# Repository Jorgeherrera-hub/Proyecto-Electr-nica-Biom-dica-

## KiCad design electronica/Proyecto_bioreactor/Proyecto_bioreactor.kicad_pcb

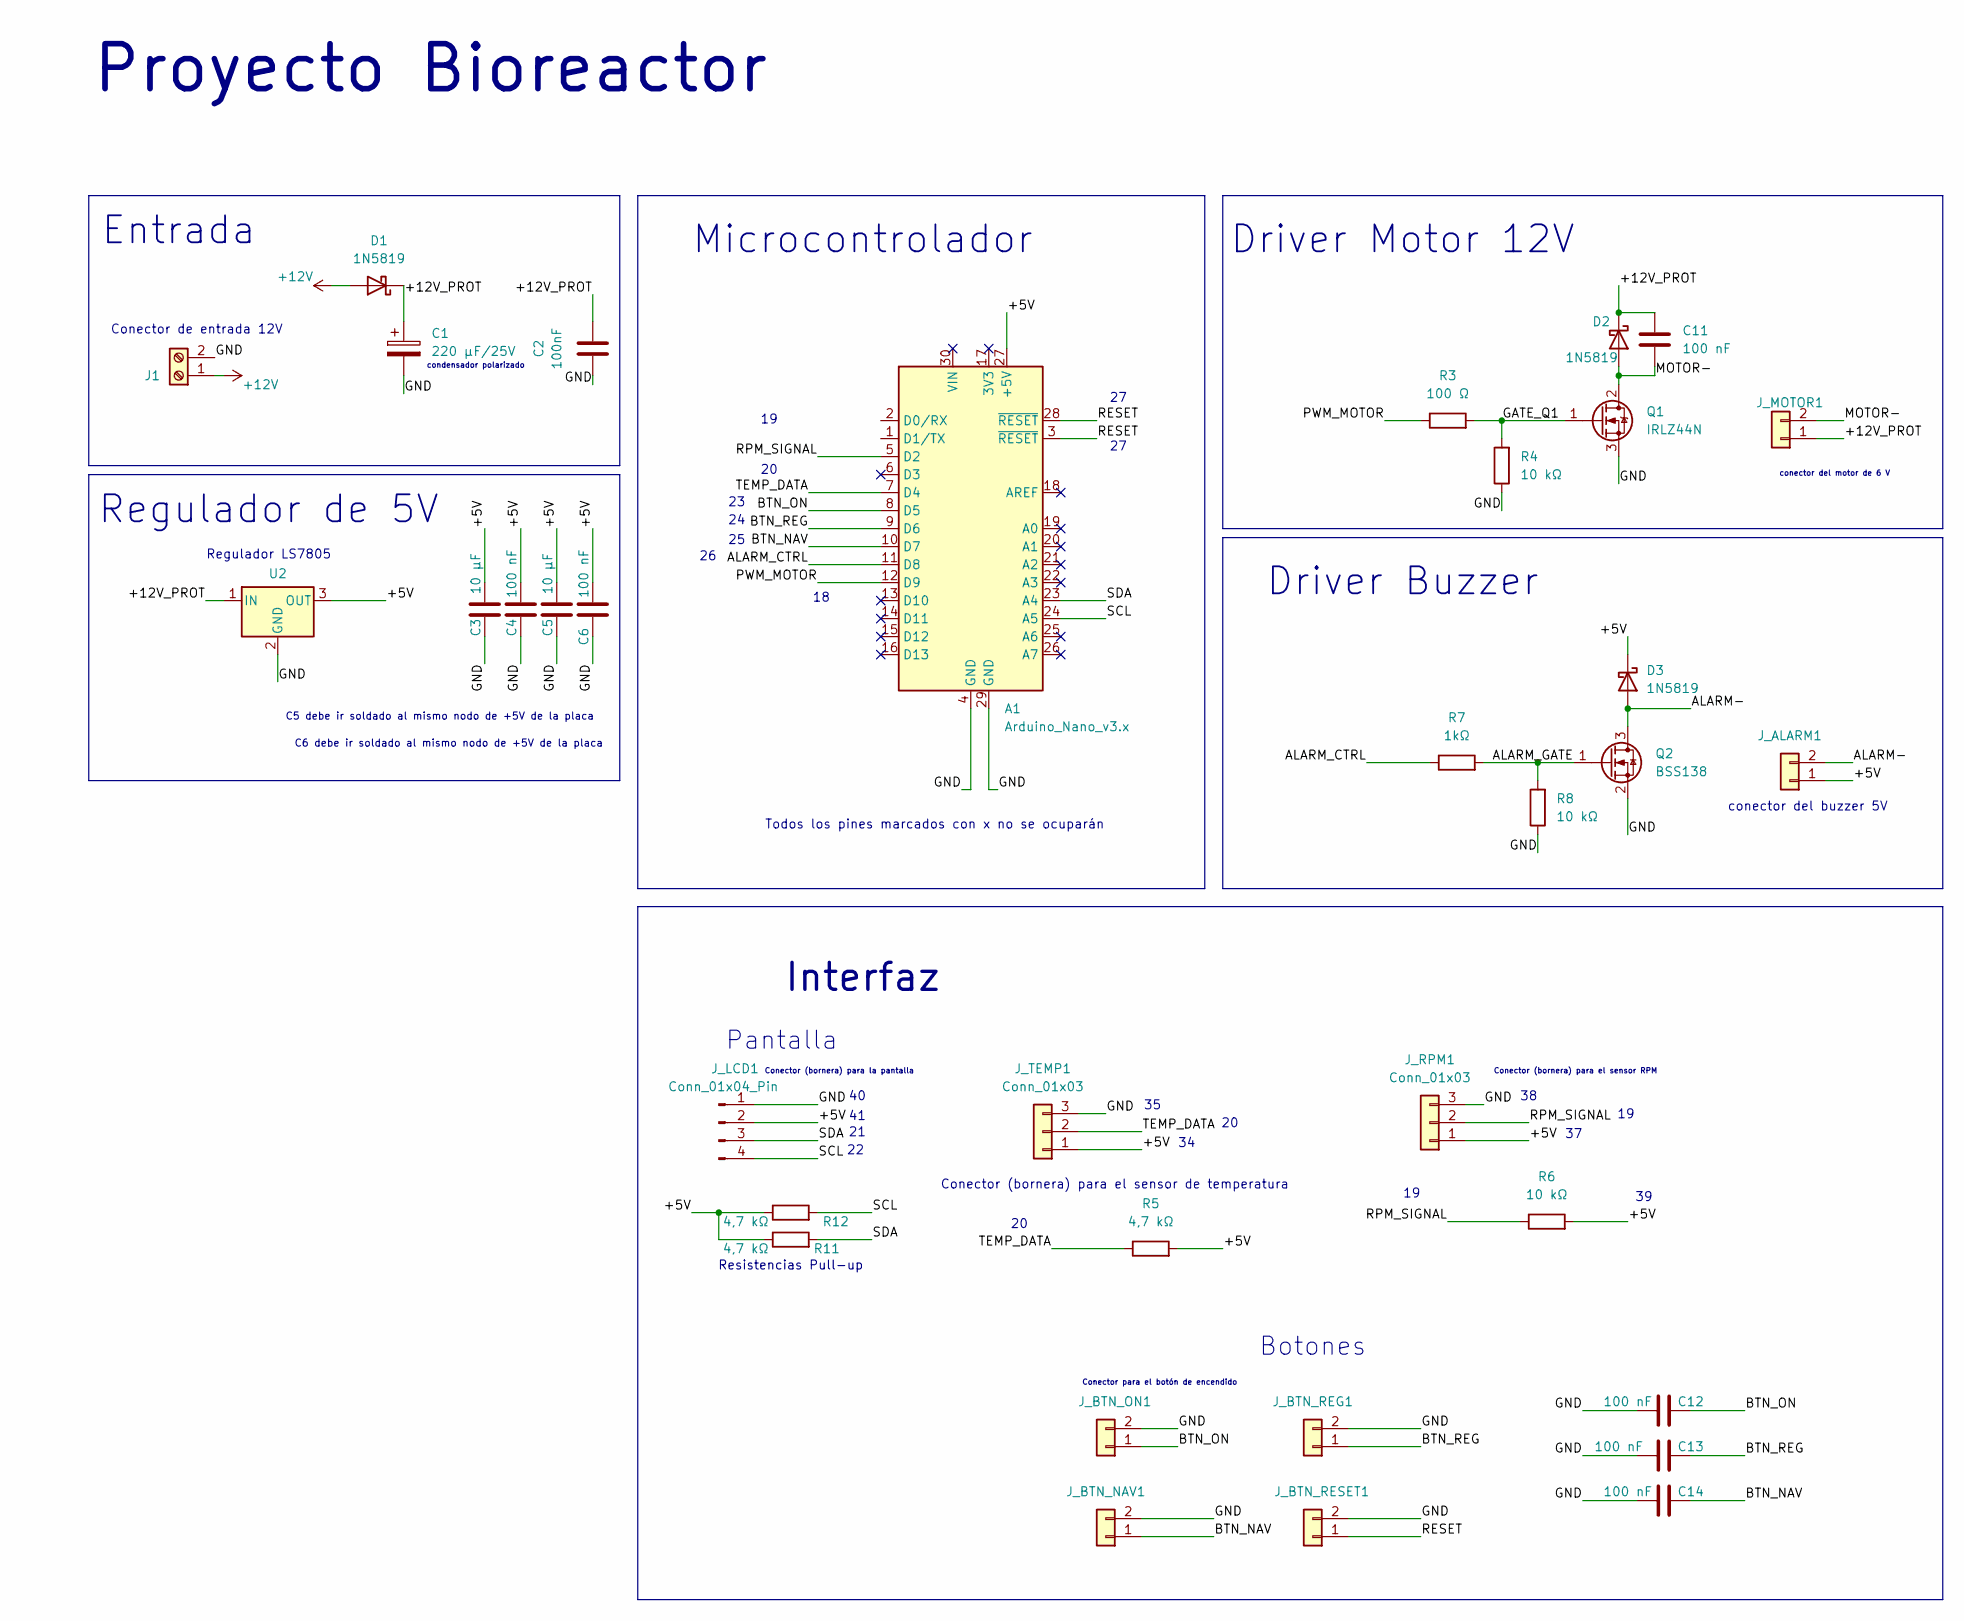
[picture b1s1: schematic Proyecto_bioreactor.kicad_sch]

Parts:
A1: Arduino_Nano_v3.x; Arduino_Nano
C1: 220 µF/25V; CP_Radial_D8.0mm_P3.50mm
C2: 100nF; C_Disc_D5.0mm_W2.5mm_P5.00mm
C3, C5: 10 µF; CP_Radial_D5.0mm_P2.00mm
C4, C6, C11, C12, C13, C14: 100 nF; C_Disc_D5.0mm_W2.5mm_P5.00mm
D1, D2, D3: 1N5819; D_DO-41_SOD81_P10.16mm_Horizontal
J1: Screw_Terminal_01x02; TerminalBlock_Phoenix_MKDS-1,5-2-5.08_1x02_P5.08mm_Horizont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
J_ALARM1: PinHeader_1x02_P2.54mm_Vertical
J_BTN_NAV1: PinHeader_1x02_P2.54mm_Vertical
J_BTN_ON1: PinHeader_1x02_P2.54mm_Vertical
J_BTN_REG1: PinHeader_1x02_P2.54mm_Vertical
J_BTN_RESET1: PinHeader_1x02_P2.54mm_Vertical
J_LCD1: Conn_01x04_Pin; PinHeader_1x04_P2.54mm_Vertical
J_MOTOR1: PinHeader_1x02_P2.54mm_Vertical; TerminalBlock_Phoenix_MKDS-1,5-2-5.08_1x02_P5.08mm_Horizont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
J_RPM1: Conn_01x03; PinHeader_1x03_P2.54mm_Vertical
J_TEMP1: Conn_01x03; PinHeader_1x03_P2.54mm_Vertical
Q1: IRLZ44N; TO-220-3_Vertical
Q2: BSS138; SOT-23
R3: 100 Ω; R_Axial_DIN0204_L3.6mm_D1.6mm_P7.62mm_Horizontal
R4, R6, R8: 10 kΩ; R_Axial_DIN0204_L3.6mm_D1.6mm_P7.62mm_Horizontal
R5, R11, R12: 4,7 kΩ; R_Axial_DIN0204_L3.6mm_D1.6mm_P7.62mm_Horizontal
R7: 1kΩ; R_Axial_DIN0204_L3.6mm_D1.6mm_P7.62mm_Horizontal
U2: OKI-78SR-5/1.5-W36-C (L7805); Converter_DCDC_Murata_OKI-78SR_Vertical

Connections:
+12V: D1.2 (A), J1.1
/+5V: A1.27 (+5V), C3.1, C4.1, C5.1, C6.1, D3.1 (K), J_ALARM1.1, J_LCD1.2, J_RPM1.1, J_TEMP1.1, R5.2, R6.2, R11.1, R12.1, U2.3 (OUT)
/+12V_PROT: C1.1, C2.2, C11.1, D1.1 (K), D2.1 (K), J_MOTOR1.1, U2.1 (IN)
/ALARM-: D3.2 (A), J_ALARM1.2, Q2.3 (D)
/ALARM_CTRL: A1.11 (D8), R7.1
/ALARM_GATE: Q2.1 (G), R7.2, R8.2
/BTN_NAV: A1.10 (D7), J_BTN_NAV1.1
/BTN_NAV: C14.1
/BTN_ON: A1.8 (D5), C12.1, J_BTN_ON1.1
/BTN_REG: A1.9 (D6), J_BTN_REG1.1
/BTN_REG: C13.1
/GATE_Q1: Q1.1 (G), R3.2, R4.2
/GND: A1.4 (GND), A1.29 (GND), C1.2, C2.1, C3.2, C4.2, C5.2, C6.2, C12.2, C13.2, C14.2, J1.2, J_BTN_NAV1.2, J_BTN_ON1.2, J_BTN_REG1.2, J_BTN_RESET1.2, J_LCD1.1, J_RPM1.3, J_TEMP1.3, Q1.3 (S), Q2.2 (S), R4.1, R8.1, U2.2 (GND)
/MOTOR-: C11.2, D2.2 (A), J_MOTOR1.2, Q1.2 (D)
/PWM_MOTOR: A1.12 (D9), R3.1
/RESET: A1.3 (~RESET), A1.28 (~RESET), J_BTN_RESET1.1
/RPM_SIGNAL: A1.5 (D2), J_RPM1.2, R6.1
/SCL: A1.24 (A5), J_LCD1.4, R12.2
/SDA: A1.23 (A4), J_LCD1.3, R11.2
/TEMP_DATA: A1.7 (D4), J_TEMP1.2, R5.1

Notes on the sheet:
Conector (bornera) para el sensor RPM
C6 debe ir soldado al mismo nodo de +5V de la placa
Pantalla
conector del buzzer 5V
Regulador de 5V
Conector de entrada 12V
Todos los pines marcados con x no se ocuparán
Conector para el botón de encendido
condensador polarizado
Driver Buzzer
Conector (bornera) para el sensor de temperatura
conector del motor de 6 V
Regulador LS7805
Botones
Interfaz
Proyecto Bioreactor
Resistencias Pull-up
Microcontrolador
Driver Motor 12V
Entrada
C5 debe ir soldado al mismo nodo de +5V de la placa
Conector (bornera) para la pantalla

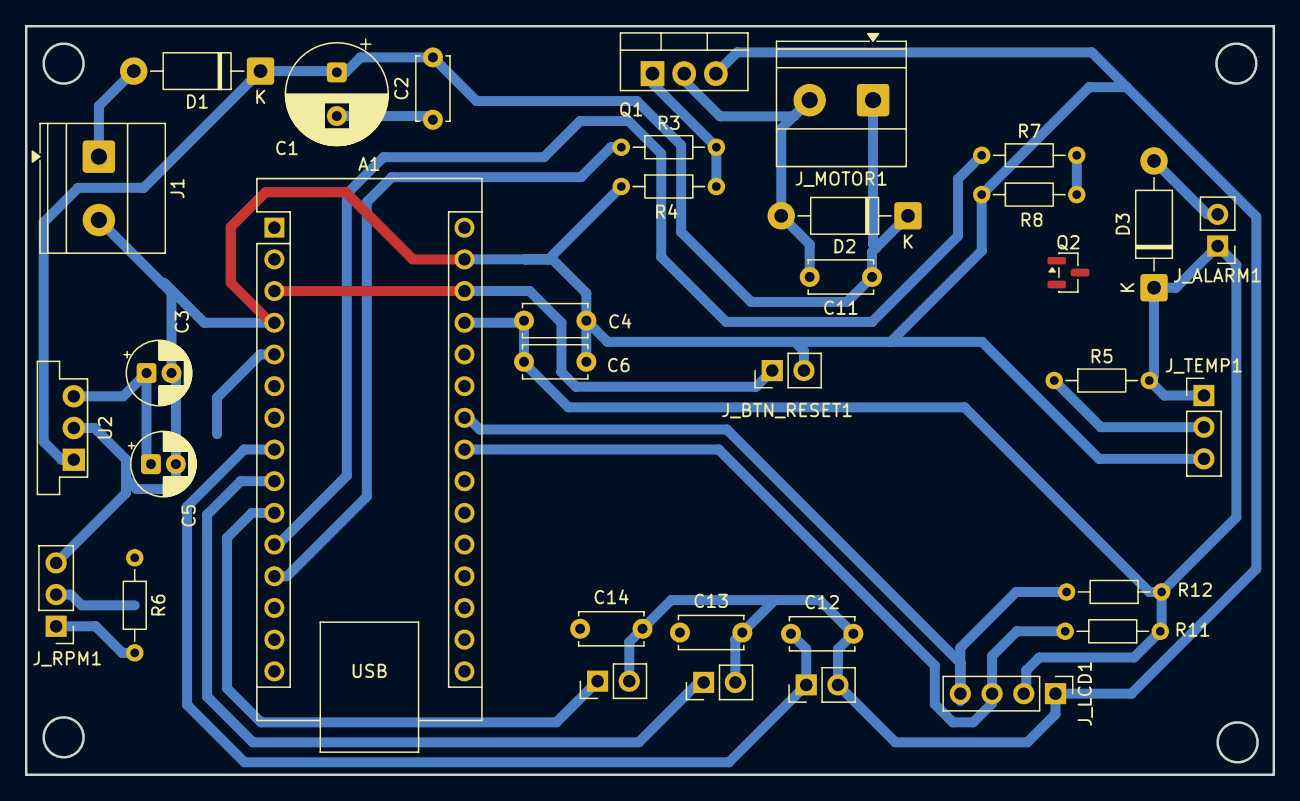
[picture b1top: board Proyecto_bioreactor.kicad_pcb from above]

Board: 2 copper layers, 100.0 x 60.0 mm, 35 parts (0 on the bottom side), 18 nets.

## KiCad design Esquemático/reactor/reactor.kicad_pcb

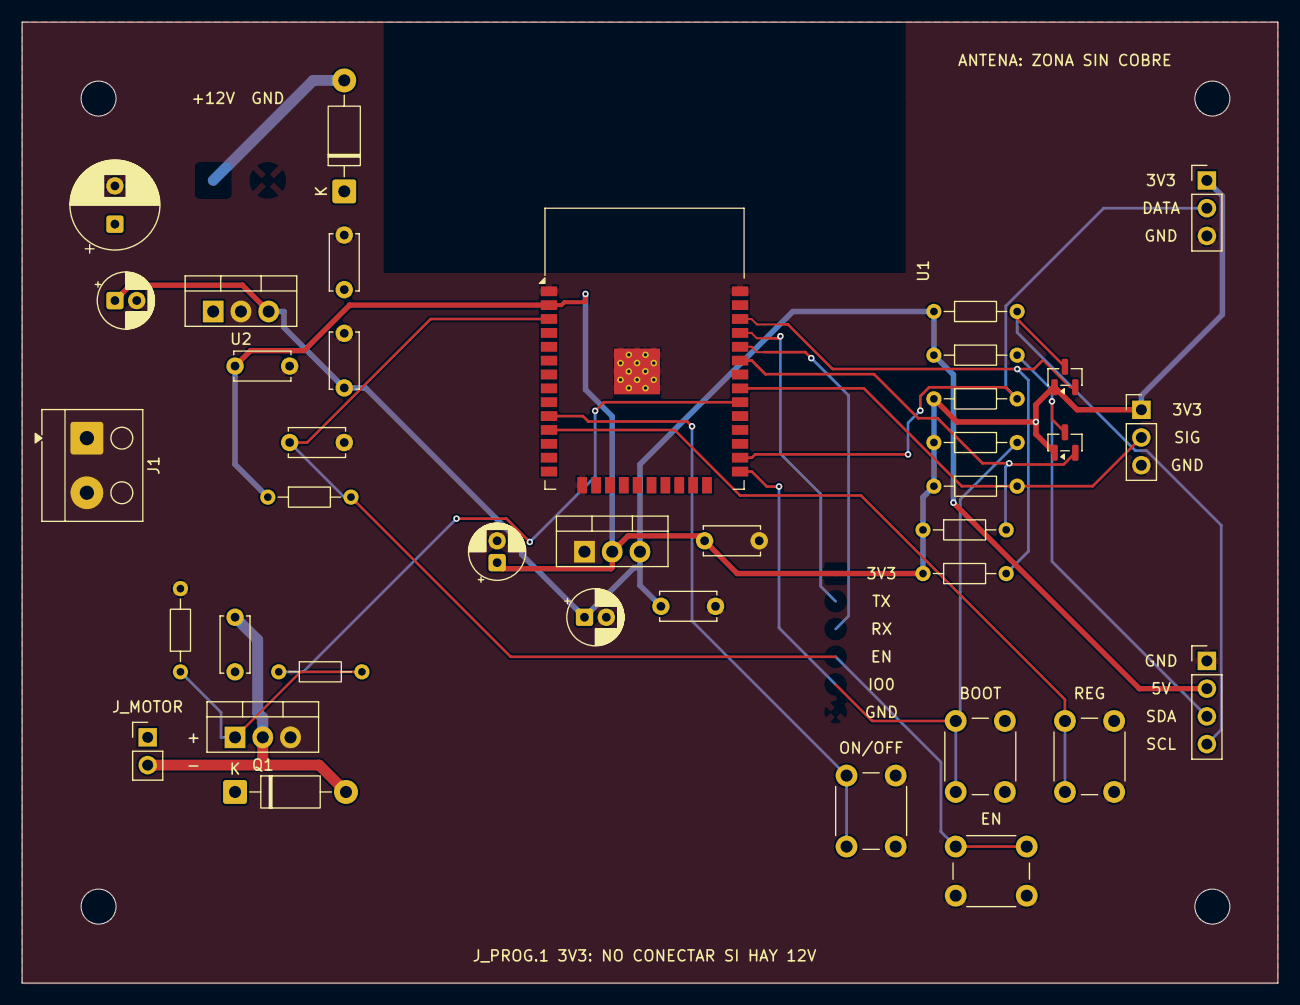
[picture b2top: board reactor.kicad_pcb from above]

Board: 2 copper layers, 115.0 x 88.0 mm, 42 parts (0 on the bottom side), 18 nets.

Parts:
C1: 220uF 25V; CP_Radial_D8.0mm_P3.50mm
C2, C4, C6, C8, C9, C10, C11: 100nF; C_Disc_D5.0mm_W2.5mm_P5.00mm
C3, C5, C7: 10uF; CP_Radial_D5.0mm_P2.00mm
D1, D2: 1N5819; D_DO-41_SOD81_P10.16mm_Horizontal
H1, H2, H3, H4: M3; MountingHole_3.2mm_M3
J1: 12V DC IN; Altech_AK100_1x02_P5.00mm
J_LCD: LCD I2C 5V; PinHeader_1x04_P2.54mm_Vertical
J_MOTOR: MOTOR; PinHeader_1x02_P2.54mm_Vertical
J_RPM: RPM SENSOR 3V3; PinHeader_1x03_P2.54mm_Vertical
J_TEMP: DS18B20; PinHeader_1x03_P2.54mm_Vertical
Q1: IRLZ44N; TO-220-3_Vertical
Q2, Q3: BSS138; SOT-23
R1, R2, R4, R6, R7, R8, R9, R10: 10k; R_Axial_DIN0204_L3.6mm_D1.6mm_P7.62mm_Horizontal
R3: 100; R_Axial_DIN0204_L3.6mm_D1.6mm_P7.62mm_Horizontal
R5: 4.7k; R_Axial_DIN0204_L3.6mm_D1.6mm_P7.62mm_Horizontal
SW_BOOT: RESET/BOOT; SW_PUSH_6mm
SW_EN: RESET/BOOT; SW_PUSH_6mm
SW_ON: PUSHBUTTON; SW_PUSH_6mm
SW_REG: PUSHBUTTON; SW_PUSH_6mm
U1: ESP32-WROOM-32
U2: OKI-78SR-5/1.5-W36-C; TO-220-3_Vertical
U3: LM1117T-3.3; TO-220-3_Vertical

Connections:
+3V3: C7.1, C8.1, C9.1, J_RPM.1, J_TEMP.1, Q2.1, Q3.1, R1.1, R2.1, R5.1, R6.1, R7.1, R9.1, U1.2, U3.2
+5V: C3.1, C4.1, C5.1, C6.1, J_LCD.2, R8.1, R10.1, U2.3, U3.3
+12V_IN: D1.2, J1.1
+12V_PROT: C1.1, C2.1, C11.1, D1.1, D2.1, J_MOTOR.1, U2.1
EN: C10.1, R1.2, SW_EN.1, U1.3
GND: C1.2, C2.2, C3.2, C4.2, C5.2, C6.2, C7.2, C8.2, C9.2, C10.2, J1.2, J_LCD.1, J_RPM.3, J_TEMP.3, Q1.3, R4.2, SW_BOOT.2, SW_EN.2, SW_ON.2, SW_REG.2, U1.1, U1.15, U1.38, U1.39, U2.2, U3.1
IO0: R2.2, SW_BOOT.1, U1.25
MOTOR-: C11.2, D2.2, J_MOTOR.2, Q1.2
unnamed: Q1.1, R3.2, R4.1
unnamed: SW_ON.1, U1.10
unnamed: SW_REG.1, U1.11
PWM_MOTOR: R3.1, U1.30
RPM_SIGNAL: J_RPM.2, R6.2, U1.31
SCL_3V3: Q3.2, R9.2, U1.36
SCL_5V: J_LCD.4, Q3.3, R10.2
SDA_3V3: Q2.2, R7.2, U1.33
SDA_5V: J_LCD.3, Q2.3, R8.2
TEMP_DATA: J_TEMP.2, R5.2, U1.26

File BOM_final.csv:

Referencias;Cantidad;Nombre real;Valor;Nombre KiCad del símbolo;Nombre KiCad de la huella;Notas
C1;1;"Condensador polarizado radial 220 µF, 25 V; fabricante y número de parte por confirmar";220uF 25V;Device:C_Polarized;Capacitor_THT:CP_Radial_D8.0mm_P3.50mm;
C2, C4, C6, C8, C9, C10, C11;7;"Condensador cerámico de disco THT 100nF; tensión nominal y número de parte por confirmar";100nF;Device:C;Capacitor_THT:C_Disc_D5.0mm_W2.5mm_P5.00mm;
C3, C5, C7;3;"Condensador polarizado radial 10uF; tensión nominal y número de parte por confirmar";10uF;Device:C_Polarized;Capacitor_THT:CP_Radial_D5.0mm_P2.00mm;
D1, D2;2;Diodo Schottky 1N5819, axial DO-41;1N5819;Device:D_Schottky;Diode_THT:D_DO-41_SOD81_P10.16mm_Horizontal;
H1, H2, H3, H4;4;Huella de agujero de montaje M3, NPTH;M3;"— (huella mecánica; sin símbolo en netlist)";MountingHole:MountingHole_3.2mm_M3;"Huella mecánica; no forma parte de la netlist eléctrica."
J1;1;"Bornera de 2 polos Altech AK300, paso 5,00 mm; número de parte comercial por confirmar";12V DC IN;Connector:Conn_01x02_Pin;TerminalBlock_Altech:Altech_AK300_1x02_P5.00mm_45-Degree;"La huella guardada es TerminalBlock_Altech:Altech_AK300_1x02_P5.00mm_45-Degree; difiere del identificador solicitado originalmente, pero representa el formato Altech AK300 de 2 pines y paso 5 mm."
J_LCD;1;"Header macho THT vertical de 04 pines, paso 2,54 mm; número de parte por confirmar";LCD I2C 5V;Connector:Conn_01x04_Pin;Connector_PinHeader_2.54mm:PinHeader_1x04_P2.54mm_Vertical;
J_MOTOR;1;"Header macho THT vertical de 02 pines, paso 2,54 mm; número de parte por confirmar";MOTOR;Connector:Conn_01x02_Pin;Connector_PinHeader_2.54mm:PinHeader_1x02_P2.54mm_Vertical;
J_PROG;1;"Header macho THT vertical de 06 pines, paso 2,54 mm; número de parte por confirmar";UART PROGRAM;Connector:Conn_01x06_Pin;Connector_PinHeader_2.54mm:PinHeader_1x06_P2.54mm_Vertical;
J_RPM;1;"Header macho THT vertical de 03 pines, paso 2,54 mm; número de parte por confirmar";RPM SENSOR 3V3;Connector:Conn_01x03_Pin;Connector_PinHeader_2.54mm:PinHeader_1x03_P2.54mm_Vertical;
J_TEMP;1;"Header macho THT vertical de 03 pines, paso 2,54 mm; número de parte por confirmar";DS18B20;Connector:Conn_01x03_Pin;Connector_PinHeader_2.54mm:PinHeader_1x03_P2.54mm_Vertical;
Q1;1;MOSFET canal N de nivel lógico IRLZ44N;IRLZ44N;Transistor_FET:IRLZ44N;Package_TO_SOT_THT:TO-220-3_Vertical;
Q2, Q3;2;MOSFET canal N BSS138, SOT-23;BSS138;Transistor_FET:BSS138;Package_TO_SOT_SMD:SOT-23;
R1, R2, R4, R6, R7, R8, R9, R10;8;"Resistencia axial THT 10k Ω; fabricante, tolerancia y potencia por confirmar";10k;Device:R;Resistor_THT:R_Axial_DIN0204_L3.6mm_D1.6mm_P7.62mm_Horizontal;
R3;1;"Resistencia axial THT 100 Ω; fabricante, tolerancia y potencia por confirmar";100;Device:R;Resistor_THT:R_Axial_DIN0204_L3.6mm_D1.6mm_P7.62mm_Horizontal;
R5;1;"Resistencia axial THT 4.7k Ω; fabricante, tolerancia y potencia por confirmar";4.7k;Device:R;Resistor_THT:R_Axial_DIN0204_L3.6mm_D1.6mm_P7.62mm_Horizontal;
SW_BOOT, SW_EN;2;"Pulsador táctil THT de 6 mm; número de parte por confirmar";RESET/BOOT;Switch:SW_Push;Button_Switch_THT:SW_PUSH_6mm;
SW_ON, SW_REG;2;"Pulsador táctil THT de 6 mm; número de parte por confirmar";PUSHBUTTON;Switch:SW_Push;Button_Switch_THT:SW_PUSH_6mm;Ambos comparten el valor PUSHBUTTON.
U1;1;"Módulo ESP32-WROOM-32 (Wi‑Fi/Bluetooth); fabricante Espressif";ESP32-WROOM-32;RF_Module:ESP32-WROOM-32;RF_Module:ESP32-WROOM-32;
U2;1;Regulador conmutado OKI-78SR-5/1.5-W36-C;OKI-78SR-5/1.5-W36-C;Regulator_Linear:L7805;Package_TO_SOT_THT:TO-220-3_Vertical;El símbolo es Regulator_Linear:L7805, usado como sustituto por compatibilidad del pinout.
U3;1;Regulador lineal LM1117T-3.3, encapsulado TO-220;LM1117T-3.3;Regulator_Linear:LM1117T-3.3;Package_TO_SOT_THT:TO-220-3_Vertical;"El pinout se toma del símbolo LM1117T-3.3; no es el pinout del 7805."
